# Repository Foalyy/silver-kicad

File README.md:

# Silver

Silver is an open-source project aiming at making a long-range and fully-featured camera remote control.

See https://silica.io/tag/silver/ for a more detailed build log of the project.

This is the repository of the Kicad project with the schematic and layout of the board. See the main repository at https://github.com/Foalyy/silver-firmware.

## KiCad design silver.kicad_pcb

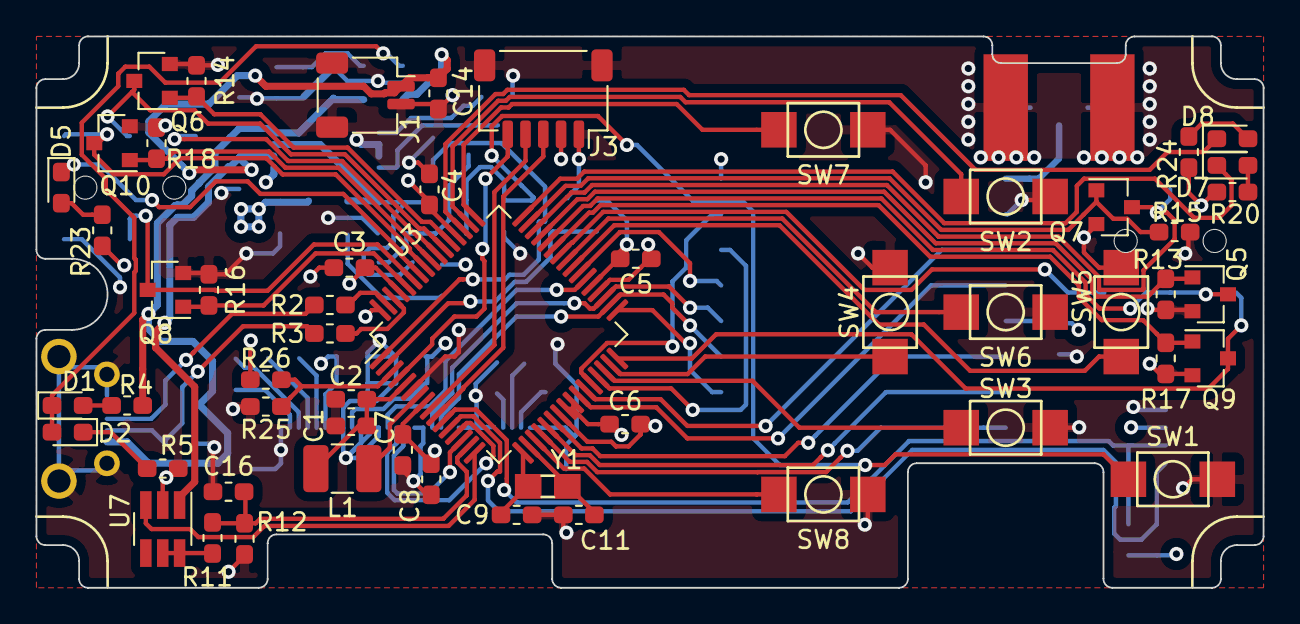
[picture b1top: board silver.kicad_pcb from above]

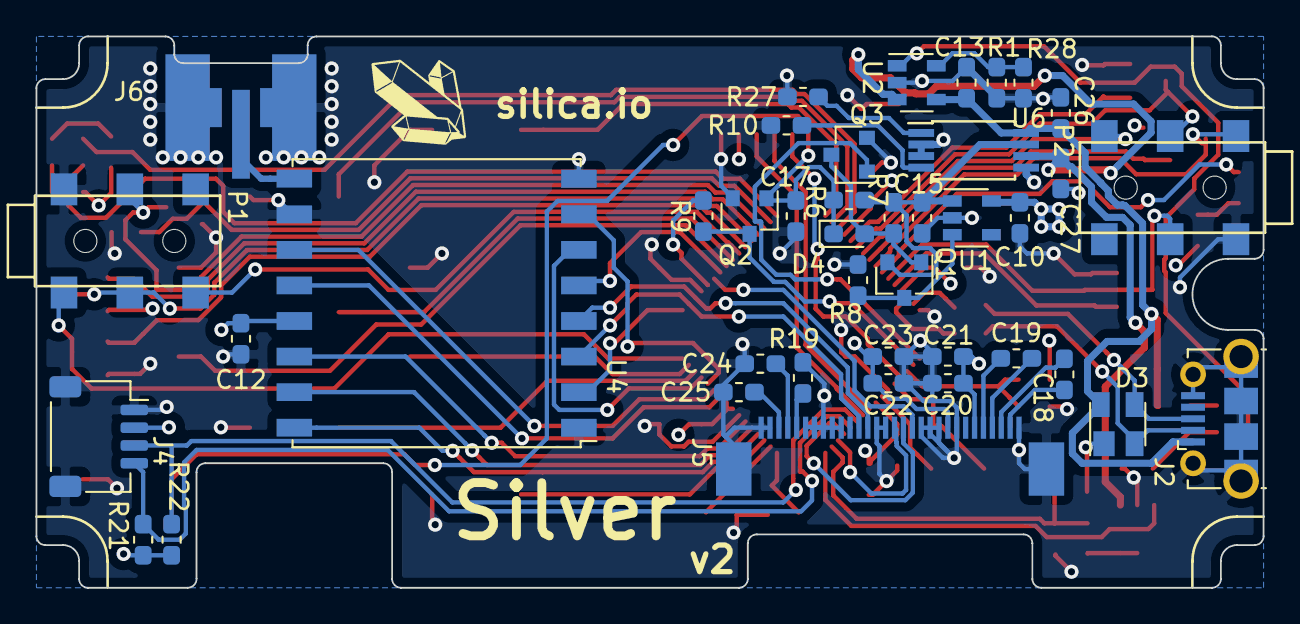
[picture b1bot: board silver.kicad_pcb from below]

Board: 4 copper layers, 69.0 x 31.0 mm, 96 parts (42 on the bottom side), 82 nets.

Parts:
C1, C3, C4, C5, C6, C7, C16, C17, C20, C22, C26, C27: 100nF; C_0603_1608Metric_Pad1.05x0.95mm_HandSolder
C2, C8, C12, C13, C14, C21, C23: 10uF; C_0603_1608Metric_Pad1.05x0.95mm_HandSolder
C9, C11: 12pF; C_0603_1608Metric_Pad1.05x0.95mm_HandSolder
C10, C15, C18, C19: 1uF; C_0603_1608Metric_Pad1.05x0.95mm_HandSolder
C24: 4.7uF 25V; C_0603_1608Metric_Pad1.05x0.95mm_HandSolder
C25: 2.2uF 25V; C_0603_1608Metric_Pad1.05x0.95mm_HandSolder
D1, D5, D7: RED; LED_0603_1608Metric_Pad1.05x0.95mm_HandSolder
D2: GREEN; LED_0603_1608Metric_Pad1.05x0.95mm_HandSolder
D3: PRTR5V0U2X; SOT-143
D4: D; D_0603_1608Metric_Pad1.05x0.95mm_HandSolder
D8: BLUE; LED_0603_1608Metric_Pad1.05x0.95mm_HandSolder
J1: Conn_01x02; JST_SH_SM02B-SRSS-TB_1x02-1MP_P1.00mm_Horizontal
J2: USB_B_Micro; USB_Micro-B_Molex-105017-0001
J3: Conn_01x05; JST_SH_SM05B-SRSS-TB_1x05-1MP_P1.00mm_Horizontal
J4: Conn_01x04; JST_SH_SM04B-SRSS-TB_1x04-1MP_P1.00mm_Horizontal
J5: Conn_01x30; FPC_30
J6: Conn_01x02; antenna_sma_ufl
L1: 22uH; L_1210_3225Metric_Pad1.42x2.65mm_HandSolder
P1, P2: jack_trrs_switch; jack_2.5_trrs
Q1: Q_PMOS; SOT-23
Q2, Q3, Q5, Q6, Q7, Q8, Q9, Q10: Q_NMOS; SOT-23
R1, R11, R12: 10KR; R_0603_1608Metric_Pad1.05x0.95mm_HandSolder
R2, R3: 39R; R_0603_1608Metric_Pad1.05x0.95mm_HandSolder
R4, R5, R10, R20, R23, R24: 470R; R_0603_1608Metric_Pad1.05x0.95mm_HandSolder
R6, R7, R8, R9, R13, R14, R15, R16, R17, R18, R27: 22kR; R_0603_1608Metric_Pad1.05x0.95mm_HandSolder
R19: 390R; R_0603_1608Metric_Pad1.05x0.95mm_HandSolder
R21, R22, R25, R28: NM; R_0603_1608Metric_Pad1.05x0.95mm_HandSolder
R26: 0R; R_0603_1608Metric_Pad1.05x0.95mm_HandSolder
SW1, SW2, SW3, SW4, SW5, SW6, SW7, SW8: Push; pushbutton
U1: TLV70233_SOT23-5; SOT-23-5
U2: MCP73831-2-OT; SOT-23-5
U3: ATSAM4LSxB; LQFP-64_10x10mm_P0.5mm
U4: LoRa_RFM9x; HOPERF_RFM9XW_SMD
U5: logo_silica; silica_logo_5mm
U6: TPS2112A; TSSOP-8_4.4x3mm_P0.65mm
U7: TPS22917; SOT-23-6_Handsoldering
Y1: Crystal_Small; quartz_abs06

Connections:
/3V3: C3.2, C4.2, C5.2, C6.2, C7.2, C8.2, C10.2, C12.1, C20.2, C21.2, C22.1, C23.1, J3.2, J4.2, J5.22, J5.25, R9.1, R20.1, R21.2, R22.1, R23.1, R24.1, R26.1, U1.5, U3.8, U3.24, U3.25, U3.37, U3.52, U3.61, U4.13
/BTN_AF: SW8.1, U3.19
/BTN_DOWN: SW3.1, U3.30
/BTN_LEFT: SW4.1, U3.31
/BTN_OK: SW6.1, U3.41
/BTN_PW: Q2.3, R9.2, U3.2
/BTN_RIGHT: SW5.1, U3.40
/BTN_TRIG: SW7.1, U3.49
/BTN_UP: SW2.1, U3.50
/LDO_IN: C15.2, Q1.2, R6.1, R7.1, U1.1, U6.7
/LED_AF: D8.1, U3.51
/LED_INPUT: D5.1, U3.58
/LED_TRIG: D7.1, U3.48
/LORA_DIO0: U3.22, U4.14
/LORA_DIO1: U3.21, U4.15
/LORA_DIO2: U3.20, U4.16
/LORA_DIO3: U3.27, U4.11
/LORA_DIO4: U3.26, U4.12
/LORA_DIO5: U3.28, U4.7
/LORA_RESET: U3.29, U4.6
/OLED_DC: J5.16, U3.14
/OLED_RES: J5.17, U3.13
/P1_R1: P1.4, Q7.3, U3.46
/P1_R1_PD: Q7.1, R15.1, U3.47
/P1_R2: P1.3, Q9.3, U3.32
/P1_R2_PD: Q9.1, R17.1, U3.43
/P1_SW: P1.7, U3.42
/P1_T: P1.6, Q5.3, U3.44
/P1_T_PD: Q5.1, R13.1, U3.45
/P2_R1: P2.4, Q8.3, U3.59
/P2_R1_PD: Q8.1, R16.1, U3.60
/P2_R2: P2.3, Q10.3, U3.57
/P2_R2_PD: Q10.1, R18.1, U3.56
/P2_SW: P2.7, U3.55
/P2_T: P2.6, Q6.3, U3.54
/P2_T_PD: Q6.1, R14.1, U3.53
/PW_EN: Q3.1, U3.1
/RST#: J3.5, U3.4
/SCL_TX: J4.4, R21.1, U3.12
/SDA_RX: J4.3, R22.2, U3.11
/SPI_CS_LORA: U3.39, U4.5
/SPI_CS_OLED: J5.18, U3.38
/SPI_MISO: U3.33, U4.2
/SPI_MOSI: J5.12, U3.34, U4.3
/SPI_SCK: J5.13, U3.35, U4.4
/SWCLK: J3.4, U3.9
/SWDIO: J3.3, U3.10
/USB_D+: R2.1, U3.63
/USB_D-: R3.1, U3.62
/VBAT: C14.2, C27.2, J1.1, U2.3, U6.6, U7.1
/VBAT_MEAS: C16.2, R11.2, R12.1, U3.15
/VBAT_MEAS_CMD: U3.16, U7.3
/VUSB: C13.2, C26.2, D3.4, J2.1, R4.2, U2.4, U6.8
/_USB_D+: D3.3, J2.3, R2.2
/_USB_D-: D3.2, J2.2, R3.2
GND: C1.2, C2.2, C3.1, C4.1, C5.1, C6.1, C7.1, C8.1, C9.2, C10.1, C11.2, C12.2, C13.1, C14.1, C15.1, C16.1, C17.1, C20.1, C21.1, C22.2, C23.2, C24.1, C25.1, C26.1, C27.1, D3.1, J1.2, J1.MP, J2.5, J2.6, J3.1, J3.MP, J4.1, J4.MP, J5.1, J5.2, J5.6, J5.7, J5.8, J5.9, J5.10, J5.14, J5.15, J5.19, J5.20, J5.21, J5.23, J5.30, J5.MP, J6.1, P1.2, P2.2, Q2.2, Q3.2, Q5.2, Q6.2, Q7.2, Q8.2, Q9.2, Q10.2, R1.2, R5.1, R8.1, R10.2, R12.2, R13.2, R14.2, R15.2, R16.2, R17.2, R18.2, R19.1, R25.1, R27.2, R28.2, SW1.2, SW2.2, SW3.2, SW4.2, SW5.2, SW6.2, SW7.2, SW8.2, U1.2, U2.2, U3.6, U3.23, U3.36, U3.64, U4.1, U4.8, U4.10, U6.2, U6.3, U6.5, U7.2
unnamed: C1.1, C2.1, L1.1, U3.5
unnamed: C9.1, U3.17, Y1.1
unnamed: C11.1, U3.18, Y1.2
unnamed: C17.2, D4.1, Q2.1, R6.2, SW1.1
unnamed: C18.1, J5.28
unnamed: C18.2, J5.29
unnamed: C19.1, J5.26
unnamed: C19.2, J5.27
unnamed: C24.2, J5.4
unnamed: C25.2, J5.3
unnamed: D1.1, D2.2, U2.1
unnamed: D1.2, R4.1
unnamed: D2.1, R5.2
unnamed: D4.2, Q1.1, Q3.3, R7.2
unnamed: D5.2, R23.2
unnamed: D7.2, R20.2
unnamed: D8.2, R24.2
unnamed: J5.5, R19.2
unnamed: J6.2, U4.9
unnamed: L1.2, U3.7
unnamed: Q1.3, R8.2, U1.3
unnamed: R1.1, R28.1, U2.5
unnamed: R10.1, U6.4
unnamed: R11.1, U7.5, U7.6
unnamed: R25.2, R26.2, U3.3
unnamed: R27.1, U6.1

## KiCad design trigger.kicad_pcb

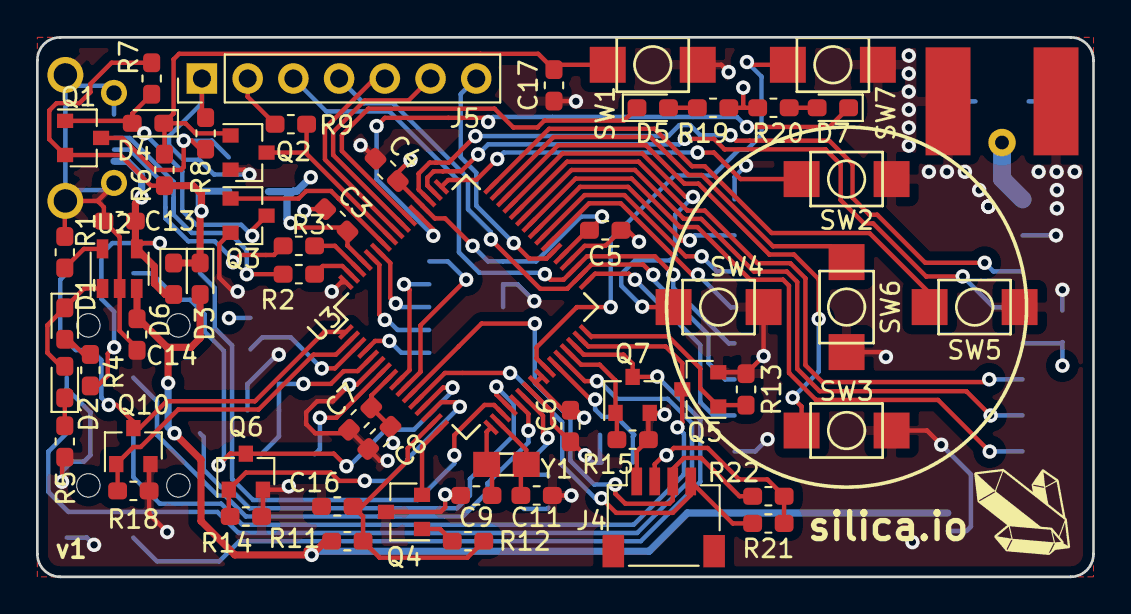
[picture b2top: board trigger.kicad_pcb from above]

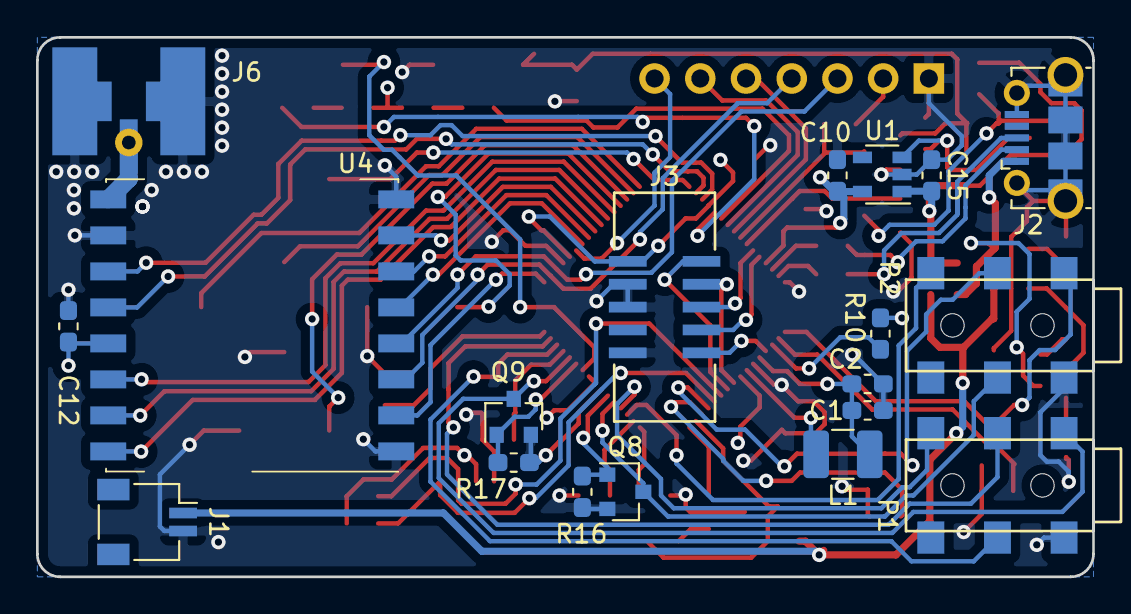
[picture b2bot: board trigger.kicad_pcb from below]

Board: 4 copper layers, 58.7 x 30.0 mm, 78 parts (19 on the bottom side), 72 nets.

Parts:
C1, C3, C4, C5, C6, C7, C16, C17: 100nF; C_0603_1608Metric_Pad1.05x0.95mm_HandSolder
C2, C8, C12, C13, C14: 10uF; C_0603_1608Metric_Pad1.05x0.95mm_HandSolder
C9, C11: 12pF; C_0603_1608Metric_Pad1.05x0.95mm_HandSolder
C10, C15: 1uF; C_0603_1608Metric_Pad1.05x0.95mm_HandSolder
D1: RED; LED_0603_1608Metric_Pad1.05x0.95mm_HandSolder
D2, D7: GREEN; LED_0603_1608Metric_Pad1.05x0.95mm_HandSolder
D3, D4, D6: D; D_0603_1608Metric_Pad1.05x0.95mm_HandSolder
D5: BLUE; LED_0603_1608Metric_Pad1.05x0.95mm_HandSolder
J1: Conn_01x02; JST_SH_SM02B-SRSS-TB_1x02-1MP_P1.00mm_Horizontal
J2: USB_B_Micro; USB_Micro-B_Molex-105017-0001
J3: Conn_02x05_Odd_Even; jtag_connector
J4: Conn_01x04; JST_SH_SM04B-SRSS-TB_1x04-1MP_P1.00mm_Horizontal
J5: Conn_01x07; oled_screen
J6: Conn_01x02; antenna_sma_ufl
L1: 22uH; L_1210_3225Metric_Pad1.42x2.65mm_HandSolder
P1, P2: jack_trrs_switch; jack_2.5_trrs
Q1: Q_PMOS; SOT-23
Q2, Q3, Q5, Q6, Q7, Q8, Q9, Q10: Q_NMOS; SOT-23
Q4: Q_NMOS_DGS; SOT-23
R1: 10KR; R_0603_1608Metric_Pad1.05x0.95mm_HandSolder
R2, R3: 39R; R_0603_1608Metric_Pad1.05x0.95mm_HandSolder
R4, R5, R19, R20: 470KR; R_0603_1608Metric_Pad1.05x0.95mm_HandSolder
R6, R7, R8, R9, R13, R14, R15, R16, R17, R18: 22kR; R_0603_1608Metric_Pad1.05x0.95mm_HandSolder
R10: 82KR; R_0603_1608Metric_Pad1.05x0.95mm_HandSolder
R11, R12: 1KR; R_0603_1608Metric_Pad1.05x0.95mm_HandSolder
R21, R22: NM; R_0603_1608Metric_Pad1.05x0.95mm_HandSolder
SW1, SW7: Push; pushbutton
SW2, SW3, SW4, SW5, SW6: SW_Push; pushbutton
U1: TLV70233_SOT23-5; SOT-23-5
U2: MCP73831-2-OT; SOT-23-5
U3: ATSAM4LSxB; LQFP-64_10x10mm_P0.5mm
U4: LoRa_RFM9x; HOPERF_RFM9XW_SMD
U5: logo_silica; silica_logo_5mm
Y1: Crystal_Small; quartz_abs06

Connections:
/3V3: C3.2, C4.2, C5.2, C6.2, C7.2, C8.2, C10.2, C12.1, J3.1, J4.2, J5.2, R9.1, R10.1, R19.1, R20.1, R21.2, R22.1, U1.5, U3.8, U3.24, U3.25, U3.37, U3.52, U3.61, U4.13
/BTN_DOWN: SW3.1, U3.46
/BTN_LEFT: SW4.1, U3.45
/BTN_OK: SW6.1, U3.47
/BTN_PW: Q2.3, R9.2, U3.57
/BTN_RIGHT: SW5.1, U3.48
/BTN_TRIG: SW7.1, U3.26
/BTN_UP: SW2.1, U3.49
/LDO_IN: C15.2, D3.1, D6.1, Q1.2, R6.1, R7.1, U1.1
/LED_PW: D5.1, U3.54
/LED_TRIG: D7.1, U3.53
/LORA_DIO0: U3.44, U4.14
/LORA_DIO1: U3.43, U4.15
/LORA_DIO2: U3.42, U4.16
/LORA_DIO3: U3.51, U4.11
/LORA_DIO4: U3.50, U4.12
/LORA_DIO5: U3.41, U4.7
/LORA_RESET: U3.40, U4.6
/OLED_DC: J5.6, U3.55
/OLED_RES: J5.5, U3.56
/P1_R1: P1.4, Q7.3, U3.30
/P1_R1_PD: Q7.1, R15.1, U3.29
/P1_R2: P1.3, Q9.3, U3.28
/P1_R2_PD: Q9.1, R17.1, U3.27
/P1_SW: P1.7, U3.20
/P1_T: P1.6, Q5.3, U3.31
/P1_T_PD: Q5.1, R13.1, U3.32
/P2_R1: P2.4, Q8.3, U3.21
/P2_R1_PD: Q8.1, R16.1, U3.22
/P2_R2: P2.3, Q10.3, U3.1
/P2_R2_PD: Q10.1, R18.1, U3.2
/P2_SW: P2.7, U3.19
/P2_T: P2.6, Q6.3, U3.13
/P2_T_PD: Q6.1, R14.1, U3.14
/PW_EN: Q3.1, U3.58
/RST#: J3.10, U3.4
/SCL_TX: J4.4, R21.1, U3.12
/SDA_RX: J4.3, R22.2, U3.11
/SPI_CS_LORA: U3.39, U4.5
/SPI_CS_OLED: J5.7, U3.38
/SPI_MISO: U3.33, U4.2
/SPI_MOSI: J5.4, U3.34, U4.3
/SPI_SCK: J5.3, U3.35, U4.4
/TCK: J3.4, U3.9
/TDI: J3.8, U3.60
/TDO: J3.6, U3.59
/TMS: J3.2, U3.10
/USB_D+: R2.1, U3.63
/USB_D-: R3.1, U3.62
/VBAT: C14.2, D3.2, J1.1, R11.1, U2.3
/VBAT_MEAS: C16.2, R11.2, R12.1, U3.15
/VBAT_MEAS_CMD: Q4.2, U3.16
/VUSB: C13.2, D6.2, J2.1, R4.2, U2.4
GND: C1.2, C2.2, C3.1, C4.1, C5.1, C6.1, C7.1, C8.1, C9.2, C10.1, C11.2, C12.2, C13.1, C14.1, C15.1, C16.1, C17.1, J1.2, J2.5, J2.6, J3.3, J3.5, J3.9, J4.1, J5.1, J6.1, P1.2, P2.2, Q2.2, Q3.2, Q4.3, Q5.2, Q6.2, Q7.2, Q8.2, Q9.2, Q10.2, R1.2, R5.1, R8.1, R13.2, R14.2, R15.2, R16.2, R17.2, R18.2, SW1.2, SW2.2, SW3.2, SW4.2, SW5.2, SW6.2, SW7.2, U1.2, U2.2, U3.6, U3.23, U3.36, U3.64, U4.1, U4.8, U4.10
unnamed: C1.1, C2.1, L1.1, U3.5
unnamed: C9.1, U3.17, Y1.1
unnamed: C11.1, U3.18, Y1.2
unnamed: C17.2, D4.1, Q2.1, R6.2, SW1.1
unnamed: D1.1, D2.2, U2.1
unnamed: D1.2, R4.1
unnamed: D2.1, R5.2
unnamed: D4.2, Q1.1, Q3.3, R7.2
unnamed: D5.2, R19.2
unnamed: D7.2, R20.2
unnamed: J2.2, R3.2
unnamed: J2.3, R2.2
unnamed: J6.2, U4.9
unnamed: L1.2, U3.7
unnamed: Q1.3, R8.2, U1.3
unnamed: Q4.1, R12.2
unnamed: R1.1, U2.5
unnamed: R10.2, U3.3

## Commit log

2019-04-15 v1 schematic and layout
2019-04-15 Added GPLv3 license
2019-04-15 Added README
2019-08-19 Layout v2
